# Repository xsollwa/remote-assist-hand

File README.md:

# remote-assist-hand
A robotic hand with pressure sensing and haptic feedback communication

**Created by:** Ruzanna Gaboyan and Philip Golczak  
**Date:** May 28, 2025  
**Demo:** https://youtu.be/ImFqXYvcVdE

## Overview
The **Remote Assist Hand** is a robotic arm with a gripping hand that is able to sense how much pressure it feels when gripping and holding objects. It uses a load cell to measure this force and sends that information to a computer through an ESP32 microcontroller. Unlike most robotic arms, **Remote Assist Hand** can *sense physical resistance and communicate it back* to the user, which helps them to know how hard the robot is gripping without directly touching anything. 

**Why we made it:** By this project we wanted to learn more about haptic feedback and *communicating the "feeling of touch"* while controlling robots. This is especially helpful for tasks that demand percision when it comes to pressure awareness: like when handling delicate objects.

## Features
- **Force sensing with load cell:** Senses how much pressure the hand feels when it grabs an object.
- **Real time feedback to computer**: ESP32 wirelessly sends data from the hand to a computer.
- **Remote control using computer**: The arm is designed to be operated remotely through a computer. 
- **Custom PCB and 3D design**: All parts including the base, casing and PCB are custom designed and printed

### Materials and Budget

| Part Number | Part Name                     | Description                         | Unit Price | Total Price |
| :---------- | :---------------------------: | :---------------------------------: | :--------: | ----------: |
| MP1         | ESP32                         | [Wi-Fi Microprocessor][1]           | $10        | $10         |
| B1          | Urgenex Lipo Battery (2x)     | [Battery for Arm and Remote][2]     | $27        | $27         |
| M1          | Digital Servo Motor (4x)      | [Servos for Joints][3]              | $45        | $45         |
| M2          | Stepper Motor                 | [Stepper for Base][4]               | $13        | $13         |
| L1          | Load Cell                     | [Load Cell for Grasper][5]          | $12        | $12         |
| A1          | Amplifier (4x)                | [Amplifier for Load Cell][6]        | $7         | $7          |
| D1          | Stepper Driver (3x)           | [Driver for Stepper][7]             | $8         | $8          |
| C1          | Hex Coupler 5mm (4x)          | [Hex Coupler for Base][8]           | $8         | $8          |
| T1          | Threaded Inserts 4mm (100x)   | [Threaded Inserts for Arm][9]       | $10        | $10         |
| BC1         | Buck Converter 4mm (2x)       | [Buck Converter for 7.4-5v][10]     | $8         | $8          |
| L1          | 5v Voltage Regulator          | [Voltage Regulator for ESP32][11]   | NA(Owned)  | NA(Owned)   |
| PCB1        | Printed Circuit Board         | [PCB for Electrical Components][12] | ~$10       | ~$10        |
| S1          | Boat Rocker Switch            | [Power Switch][13]                  | $5         | $5          |
| TOT         | Total (Excluding taxes, shipping and fees)         |               |            | $163        |

[1]: https://www.amazon.com/HiLetgo-ESP-WROOM-32-Development-Microcontroller-Integrated/dp/B0718T232Z/ref=sr_1_7?crid=3215NDM97THDZ&dib=eyJ2IjoiMSJ9.XBINg-sjhfF_gUtnMiKGjhlE-f5AuPRamTr33nRxSXkGLv_o48kwC8Ijeis6JInJV0KyHBRH7xGJQ-1txsZL4_5QVucvaXvokYACu1kJYTispfjw86LMs4pUaEb3QBf2tCHnMbfhxKmN1GqPyMwCe0JXg3RkQWr3XzxjTqvRC2Vi1yxUnR4MgBHJZC4l4B3sckUL9U6HKhcOjM0hclVNu3VH8A-i1EauSL7KfuJcGiQ.nLKf6GH-ppYlGRm2A-K7bqKU-ETPi6PvqRFLruHjBsE&dib_tag=se&keywords=esp+32&qid=1749497283&sprefix=esp+%2Caps%2C96&sr=8-7

[2]: https://www.amazon.com/URGENEX-Battery-1800mAh-Rechargeable-Campatibal/dp/B0924MM61Z/ref=sxin_17_sbv_search_btf?content-id=amzn1.sym.8aea4788-5372-43c5-bde7-3d239eb02a51%3Aamzn1.sym.8aea4788-5372-43c5-bde7-3d239eb02a51&crid=3Q08CKQ0G2YS0&cv_ct_cx=2s+lipo&keywords=2s+lipo&pd_rd_i=B0924MM61Z&pd_rd_r=2fee5f48-be65-4bef-8665-56cf135858b5&pd_rd_w=GqGDQ&pd_rd_wg=o6vhg&pf_rd_p=8aea4788-5372-43c5-bde7-3d239eb02a51&pf_rd_r=TBJT25WAE9YMH6TNV576&qid=1748989214&sbo=RZvfv%2F%2FHxDF%2BO5021pAnSA%3D%3D&sprefix=2s+lipo%2Caps%2C112&sr=1-1-5190daf0-67e3-427c-bea6-c72c1df98776

[3]: https://www.amazon.com/HOOYIJ-Digital-Waterproof-Crawler-Control/dp/B0CJ79WBZ8/ref=sr_1_1_sspa?crid=II8P79I7EU3N&dib=eyJ2IjoiMSJ9.RXNjcMfukzphkBNoxQhGl_2X6CMO6OywX0AKSLnJTmeO5sbO5mpsm-EwA_kGf1xVZiEEhk85jOmUElccdUoRWNgNUme1xQ4jua08F_d2wLCjJRiKMjH0Qs5Nxg4-KXBXNzY6OAMlC3yu9rLEan4Fx9IY-3VLuXghMXE15RnSJWjjP182cTMMj0EvmzgiH4Pu6tx4Y4sVvq7ACK8OX0gFo9Jm8_4Ke6n-Jc1n8Ft_J9oZNGEQYPsl1raHdnH92lMm6qLhOzlZq2tfRI-3Fv_b4goplxWY2-O_tHleHcBNQ6Q.8lEwTl6zDFn8bZzGeaELR1WADyrlU3GagRHsQIBNkJc&dib_tag=se&keywords=DS3218&qid=1748997128&s=toys-and-games&sprefix=ds3218%2Ctoys-and-games%2C117&sr=1-1-spons&sp_csd=d2lkZ2V0TmFtZT1zcF9hdGY&psc=1

[4]: https://www.amazon.com/Stepper-Motor-Bipolar-64oz-Printer/dp/B00PNEQI7W/ref=sr_1_13?dib=eyJ2IjoiMSJ9.hN-9QQUUabt-Xybqh_2heY2GPNfYHPQMKSJH70tSBpIM8bybf-KecB6p_pxJoro1zGUosznFlsHJGc4on5aqOInchCuQE03s3Tv82JFYp9OWAB4l0xbrW9FDe5ooLQbYz0cwo4oCwpUYSGTl5W1OckKUWi1IJi_aAwCMhXgjy6ntsMQ8aII6maudcs5NUerZw9xJs8-OMItZL7xCJTZ6BK19N3MhNraiCAqmrDg8X7o.ymAC-I-yPi_yIlLZG5H5tpNB5KNk5S32itGJGedbwRA&dib_tag=se&keywords=NEMA+17&qid=1749003870&sr=8-13

[5]: https://www.amazon.com/uxcell-Weighing-Electronic-Balance-Sensor/dp/B07NS81RT6/ref=sr_1_2_sspa?dib=eyJ2IjoiMSJ9.AyZAt824I6dryU0O2Zu-yQ.-DyDHOiu_BLkLqfgqd2o3Xdxj2b2zMU2XIF6RFUpfR4&dib_tag=se&keywords=tal221&qid=1749148994&sr=8-2-spons&sp_csd=d2lkZ2V0TmFtZT1zcF9idGY&psc=1

[6]: https://www.amazon.com/WWZMDiB-HX711-Amplifier-Displacement-Acceleration/dp/B0BLND4VF6/ref=sr_1_3?crid=3FCALBMD1NR0E&dib=eyJ2IjoiMSJ9.eiLmQONt8tFAyUMm-av_6RdCsR0ZVS6cJHb3ab0ccsjR7oUrIqa-VHcLN3xcpOBlpc_08WHh62HHxlddYW1rA7AGZePv1Cyp0q7kvRdA575RbT9tRyBD8S_x9a3K1TIBK4OgxY_OloVaStxeZeWM9P9lfdVwri_Ek0AVYYuIfkR_euvRR2siY9ns1faktgc_zx-CT5MLj_ikhGnw8v33mKswr2r0VuugJpcO1_d13_8.eypDpwmpp6q0xhYlaQGg9oeoRt-guQy3EfPsYo_eLn4&dib_tag=se&keywords=load+cell+amplifier&qid=1749149193&sprefix=load+cell+amplifier%2Caps%2C103&sr=8-3

[7]: https://www.amazon.com/WWZMDiB-Stepstick-Stepper-Printer-Suitable/dp/B0BFQZWT6R/ref=sr_1_13?crid=3RVK8J66P0VYW&dib=eyJ2IjoiMSJ9.S3VjKfGcCiwNSTXBu7tAhHANgI7IT5tMpRzke8Y_UGA45Q0cmTps8iDc5MYrb7OAB1BuIV3-ckwB_1tW61WLv75lK1qriRV_gCtyF8pK9AAigJ4T8KIgMD-lC6rjFR3vqUPIYj-krOmZSAoc4195flDYsN-LHi0lqnITOSGF0FtA9IkSMC34aQSZkxVQLKAUyfdankYcJSQyb52NpO_MOIe67VMMmMAIz6wi56Zj7jM.ql0iLZTvuvilgX5DbTH-PhOZY2qf9PCNg652MDi5t1U&dib_tag=se&keywords=stepper%2Bmotor%2Bdriver&qid=1749149399&sprefix=stepper%2Bmotor%2B%2Caps%2C109&sr=8-13&th=1

[8]: https://www.amazon.com/uxcell-Coupler-Coupling-Connector-Wheels/dp/B08M379TCT/ref=sr_1_3?crid=2NI5R9L70ANGS&dib=eyJ2IjoiMSJ9.kREQIRc-yoHDO809lQhudfKU49fcw3VGYy6XX8GBcoml01Yc6pcpW18aygFuzty-3JkjVgRCWnsnUluZOcFF7DWUYlbC61-76O4XxyIJxm8kKEHA8KpnP3QtSJ__uo_6MhLSX8DJRXSijKjPKo32FAlgUkGWMF3r5ozkvdE-hNpI68fUXJ1kKNpRGfH-BTgWqnWBxH0pqqZvQmurcEXNmEQ-cw9RV47iP3Yim_MCSbz3pCw_1rei_3tTU-agr2LSjWUNB1eK0vXPidK_nHUSRDkMLiubl59YmnVboFk73k8.DEPGpLJoM_TEDqWvkzBwgolyDYY_VbsG9Z_xcY1JYyk&dib_tag=se&keywords=5mm%2Bshaft%2Bhex%2Badapter&qid=1749745924&sprefix=5mm%2Bshaft%2Bhex%2Badapte%2Caps%2C94&sr=8-3&th=1

[9]: https://www.amazon.com/HANGLIFE-Heat-Set-Threaded-Printing-Components/dp/B0CS6XGMFD/ref=sr_1_3?crid=PVU86WNJN8K3&dib=eyJ2IjoiMSJ9.mB9ah2DA1qODSy-KL_pRCQWxCkecQxuEGXX9mJTJKCUJMGp9myJf9McuydE0AnN8f4EKIGs1Q8q3M8ieEczTGdJ13JbRxSiQE2sLb1ek7ToxczyKeuNZ-4xtx7_Nkmf0hIfnjSWSdG_xlNtZ1DsZAI_y9vv3TrZzWsA0HXoQq3P9OFhXKtfXvLXLGkaHfN0IIJXw0MS5Ue0_xa5BlGvw0y-H1F4ClSGtFm30JwdPwWs.lnuZpXlqxKO7YUl6IQ5QYgLlQsRhRtVeCl3jy4BCWn4&dib_tag=se&keywords=4m%2Bthreaded%2Binserts&qid=1749758810&sprefix=4m%2Bthreaded%2Binserts%2Caps%2C110&sr=8-3&th=1

[10]: https://www.amazon.com/Maxmoral-Converter-Adjustable-Step-Down-Regulator/dp/B07MKQXNWG/ref=sr_1_8?crid=2O8Z0895WHHXP&dib=eyJ2IjoiMSJ9.Mn8RJg1NDqimTO87a_6HSzNLUgHkiPZ-VHvhyk_sEEX959uBLCpsnr1INDbSWpDKHzBUeE-YTWH4jJPt8yN_66qJGG0LMLLCtm2hUaRa0Z7giRo_BbYZ43KzK8a0ZkmFgm1_7exLw-T5nEHN_xsRLts72GEUkHbbKW-mQhQgRSSwipKjFBaNXV0R6c9MMWTGuIFDt9opV19PQrMrfOmi0de15Fu1fMhiF38ZXDObWWI.BWYEDRp61inwdzt085fWsmer4meqyVfUpvTSosCXECM&dib_tag=se&keywords=buck+converter+7.4v+to+5v&qid=1749758952&sprefix=buck+converter+7.4%2Caps%2C125&sr=8-8

[11]: https://www.amazon.com/BOJACK-Regulator-Integrated-Circuits-Regulators/dp/B07VRS9HW4/ref=sr_1_1_sspa?crid=1FMO0QG5426K&dib=eyJ2IjoiMSJ9.3DvM6EEjT0E8lIvO5bv0m0l5-9vUVLBlgJTHSeOjCq0A7p4ed2I2C-vAxzaLxxhWGyJqyTu71RqUGk3fMci5qo7B5BjxWHmq1K2d8rRrYi1mG5E2VtX9murMMvM2fUVQYHqiK3mt2-U9DQX644BlvY4EyH8BJPcOVBnM89k5KlWSC2pmqDFq7ciuwvBZ9IRSGREYlW4TB0gLkCzX_hV0TAcuWhxb3T6hb7xzGx_z-Fk.3h4V044RcVNM6ZSOOjiVCJjClQfxuqAr8VHLddswSGw&dib_tag=se&keywords=5v+linear+regulator&qid=1749767656&sprefix=5v+linear+r%2Caps%2C92&sr=8-1-spons&sp_csd=d2lkZ2V0TmFtZT1zcF9hdGY&psc=1

[12]: https://cart.jlcpcb.com/quote?orderType=1&stencilLayer=4&stencilWidth=80&stencilLength=80&stencilCounts=5&spm=Jlcpcb.Homepage.1010&spm=Jlcpcb.Instantquote&_t=1750400179249&up_spm=Jlcpcb.Loginpage.1003

[13]:https://www.amazon.com/10PCS-Rocker-Switch-Rectangle-Black/dp/B094FWYWL5/ref=pd_rhf_se_s_pd_sbs_rvi_d_sccl_2_3/140-6042190-5323536?pd_rd_w=4WVy0&content-id=amzn1.sym.6640a844-ab24-4352-ac9b-78899e683a5e&pf_rd_p=6640a844-ab24-4352-ac9b-78899e683a5e&pf_rd_r=DR52KG0H5RJ4PCX9CGEN&pd_rd_wg=gzPh0&pd_rd_r=7d525b38-a4b4-48b6-9cf1-d10f36e6cb2b&pd_rd_i=B094FWYWL5&th=1

### Notes on Purchasing and Shipping
We want to purchase most of the parts from Amazon. We chose Amazon as our primary supplier because we have access to Amazon Prime, which has faster and free shipping. The free shipping makes the packs cheaper than the singular alternatives at other sources. Some components, like the voltage regulators, were only available in multi packs, so the unit price listed is price of the whole pack. Also, we plan to use some of the parts, like the battery and voltage regulators, for our next project, so their cost is shared across multiple builds!

## How it Works
1) Servo motors (controlled from a computer) move the arm and the gripper to **hold an object**,
2) The load cell inside the gripper **measures how much force** is being applied,
3) ESP32 **sends the data to a computer** in real time,
4) The computer **displays the pressure**, helping the user understand how hard the robot is gripping.

## Pictures 

**Overview Wiring Diagram**

**PCB**

**3D model**

**Build IRL**

## Building Process
1) Brainstorming and sketching
2) PCB Design using KiCAD 
3) CAD Modeling using OnShape
4) Revision and Optimization
5) Assembly and testing

## Journal
Our full development journal can be found [here](./JOURNAL.md) (includes what we struggled with and what we learnt)

## Contact
For any questions or suggestions please reach out to us at *gaboyanruzanna@gmail.com* or *ph.golczak@gmail.com* .

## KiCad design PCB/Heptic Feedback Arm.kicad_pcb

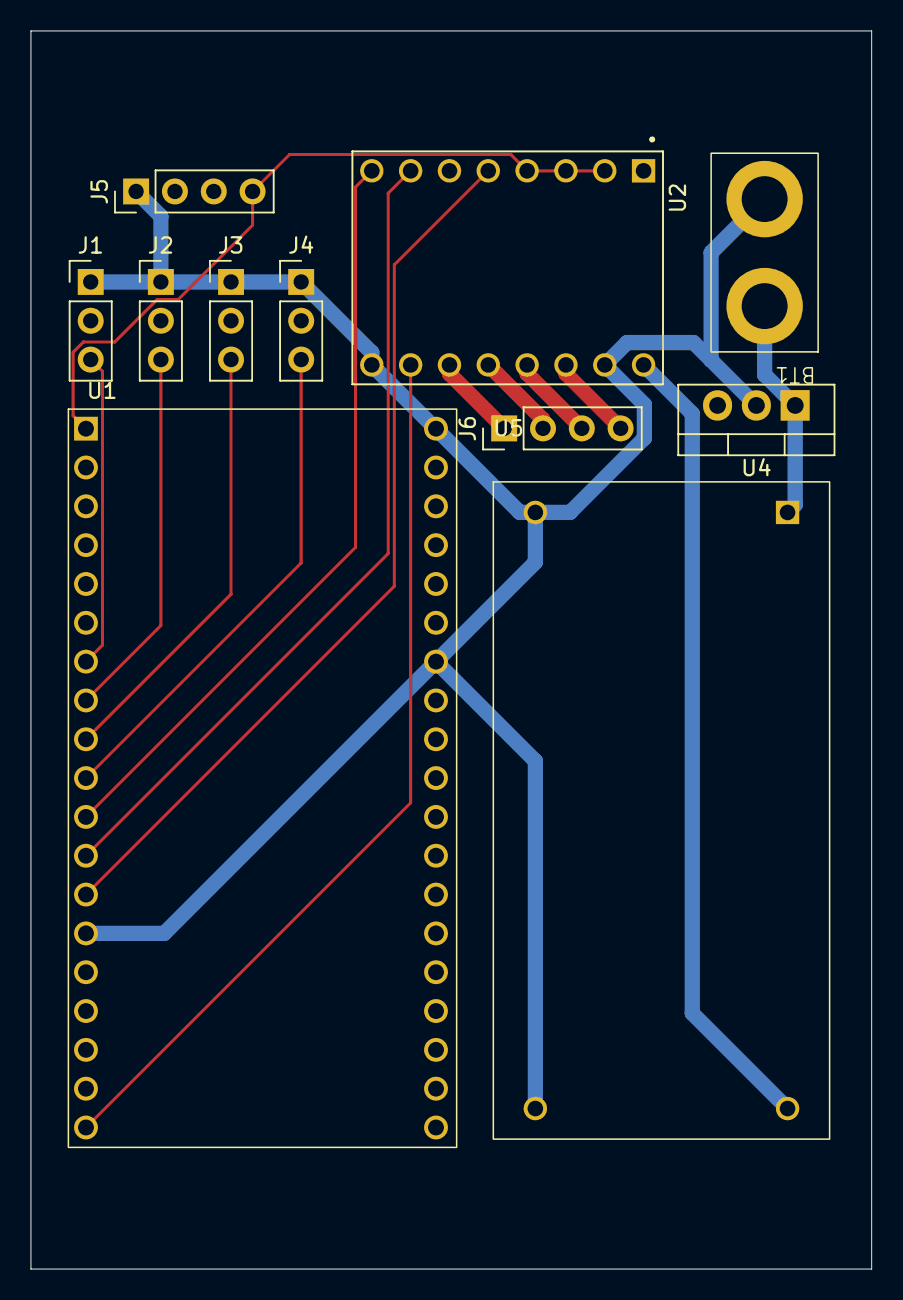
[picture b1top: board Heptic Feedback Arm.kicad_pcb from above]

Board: 4 copper layers, 55.0 x 81.0 mm, 11 parts (0 on the bottom side), 18 nets.

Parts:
BT1: Battery_Cell; Lipo Battery T Plug
J1: Servo 1; PinHeader_1x03_P2.54mm_Vertical
J2: Servo 2; PinHeader_1x03_P2.54mm_Vertical
J3: Servo 3; PinHeader_1x03_P2.54mm_Vertical
J4: Servo 4; PinHeader_1x03_P2.54mm_Vertical
J5: Load Cell Amp; PinHeader_1x04_P2.54mm_Vertical
J6: Stepper Motor; PinHeader_1x04_P2.54mm_Vertical
U1: ESP32-DEVKITC-32D; ESP32_1
U2: A4988_STEPPER_MOTOR_DRIVER_CARRIER; MODULE_A4988_STEPPER_MOTOR_DRIVER_CARRIER
U4: L7805; TO-220-3_Vertical
U5: Buck_Converter; Buck Converter

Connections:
+3.3V: J5.4, U1.J2-1 (3V3), U2.2 (MS1), U2.3 (MS2), U2.4 (MS3)
+5V: U1.J2-19 (EXT_5V), U2.10 (VDD), U4.3 (OUT)
+6V: J1.2, J2.2, J3.2, J4.2, U2.16 (VMOT), U5.4 (OUT+)
/1A: J6.4, U2.12 (1A)
/1B: J6.3, U2.11 (1B)
/2A: J6.2, U2.13 (2A)
/2B: J6.1, U2.14 (2B)
/VBAT: BT1.1 (+), U4.1 (IN), U5.1 (IN+)
GND: BT1.2 (-), J1.1, J2.1, J3.1, J4.1, J5.1, U1.J2-14 (GND1), U1.J3-1 (GND3), U1.J3-7 (GND2), U2.9 (GND), U2.15 (GND), U4.2 (GND), U5.2 (IN-), U5.3 (OUT-)
unnamed: J1.3, U1.J2-7 (IO32)
unnamed: J2.3, U1.J2-8 (IO33)
unnamed: J3.3, U1.J2-9 (IO25)
unnamed: J4.3, U1.J2-10 (IO26)
unnamed: J5.2, U1.J3-9 (IO18)
unnamed: J5.3, U1.J3-8 (IO19)
unnamed: U1.J2-13 (IO12), U2.5 (~RESET)
unnamed: U1.J2-12 (IO14), U2.7 (STEP)
unnamed: U1.J2-11 (IO27), U2.8 (DIR)

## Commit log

2025-05-28 Created the JOURNAL.md
    Created the JOURNAL.md file to journal the progress of brainstorming, designing and building the robotic arm.
2025-05-28 Updated the JOURNAL.md with initial information about the project
2025-05-28 Update JOURNAL.md (Day 1!)
2025-05-29 Update README.md
    Added intro, overview, features, journal and contact info
2025-06-04 Updated MATERIALS-AND-BUDGET
2025-06-04 Update JOURNAL.md (Day 2)
2025-06-04 Update JOURNAL.md (Day 3)
2025-06-04 Update JOURNAL.md (June 4 Ruzanna)
2025-06-05 Updated MATERIALS-AND-BUDGET.md
2025-06-06 Updated JOURNAL.md (June 5)
2025-06-07 Update JOURNAL.md (June 6 Ruzanna)
2025-06-09 Updated MATERIALS-AND-BUDGET.md (June 9)
2025-06-09 Updated MATERIALS-AND-BUDGET.md Prices (June 9)
2025-06-12 Updated JOUNRAL.md (June 11)
2025-06-12 Updated MATERIALS-AND-BUDGET.md (June 12)
2025-06-13 Updated JOUNRAL.md (June 12)
2025-06-13 Updated JOURNAL.md (image fix)
2025-06-13 Updated JOURNAL.md (Image names June 13)
2025-06-13 Updated JOUNRAL.md (Image fix again)
2025-06-13 Updated JOURNAL.md (June 13)
2025-06-15 Update README.md (June 15)
2025-06-15 Update JOURNAL.md (June 15)
2025-06-20 Create file
2025-06-20 Create images
2025-06-21 Updated JOURNAL.md Added Production Files Added CAD Files (June 20)
2025-06-21 Updated JOURNAL.md (June 20)
2025-06-21 Updated CAD founder (June 20)
2025-06-21 Updated PCB Folder (June 20)
2025-06-21 Updated README.md (June 20)
2025-06-21 Updated README.md and PCB foulder (June 20)
2025-06-21 Updated File Names in PCB Folder (June 20)
2025-06-24 Created and Filled out Code Folder and Updated README (June 24)
2025-06-25 Updated README.md and JOURNAL.md (June 24)
2025-06-25 Updated README.md (June 24)
2025-06-25 Updated BOM.csv (June 25)
2025-07-11 Updated Code Folder (July 10)
2025-07-30 Updated Code (July 30)
2025-08-05 Updated Code (August 5)
2025-08-06 Updated Code (August 6)
2025-08-06 Updated JOURNAL.md (August 6)
